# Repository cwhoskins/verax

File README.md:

# Verax

**Warning** This repo is under heavy design and should not be used under the belief that anything is stable or fully fleshed out.

Verax lets you describe a circuit, state what it must do, and check that by simulation. It is an embedded DSL in a Nim library: a design is a `.nim` file that declares nets, parts and subcircuits alongside the claims they must meet, and `verax check` proves or disproves each claim with graph walks, ngspice runs or a native signal-integrity engine.

The language is highly parameterizable and hierarchical in nature. Designs should be composed of subcircuits which have factory methods for design decisions and connected via standard interfaces and buses whenever possible.

## Example

```nim
import verax/contract/dsl
import verax/verify

let d = design("divider"):
  net gnd, kind = ntGround, name = "0"
  net vin, kind = ntPower:
    spec:
      voltage = 12.0.V
  net mid, kind = ntSignal

  component V1, kind = "voltage_source", value = "DC 12":
    pin "+", vin, kind = ptPower
    pin "-", gnd, kind = ptGround
  component R1, kind = "resistor", value = "30k":
    pin "1", vin, kind = ptPassive
    pin "2", mid, kind = ptPassive
  component R2, kind = "resistor", value = "10k":
    pin "1", mid, kind = ptPassive
    pin "2", gnd, kind = ptPassive

  role "power_rail", supply, rail = vin, voltage = 12.0.V, band = 5.pct
  require dc_voltage(mid) == 3.0.V, band = 1.pct, id = "REQ-DIV-TAP-001",
          because = "two 1% resistors give 1% worst case"

quit(verifyMain(d))
```

```
$ verax check templates/divider.nim
  spice.dc_voltage  [.op]  --  2 claim(s): 2 met
    [PASS]  REQ-DIV-TAP-001   dc_voltage(net 'mid')
             expect 3.00 V +-1.00% (2.97 V .. 3.03 V)   measured 3.00 V
    [PASS]  supply.voltage   dc_voltage(net 'vin')
             expect 12.0 V +-5.00% (11.4 V .. 12.6 V)   measured 12.0 V

checked 2 assertion(s): 2 passed, 0 failed, 0 not evaluated, 0 not evaluable
```

The full, commented version is `templates/divider.nim`.

## Features
- **Design contracts**: `role` bundles and `require` claims state what a circuit must do; each claim carries its tolerance band, an ID and a `because`. Static checks run without a simulator (`--offline`), and `--strict` fails on anything left unchecked
- Pin muxing built into parts and pin decisions automatically validated against the pin muxing table
- Standard interfaces automatically infer schematic analysis and auto-generated SPICE simulations
- **SPICE simulation** through ngspice (`.op`, `.dc`, `.ac`, `.tran`), with simulation-only device models and XSPICE code models (analog and digital) authored from Nim
- **Native signal-integrity engine** (no ngspice): IBIS drivers and receivers, packages, transmission lines and vias, crosstalk, differential pairs, PRBS/eye analysis and S-parameter channels
- IBIS sweeps pre-layout derive routing constraints, written out as KiCad `.kicad_dru` rules (`verax constraints`); `si_net` claims are then checked against the routed board (`--board=`)
- **Test reports**: `verax report` writes one self-contained HTML (or PDF) file with each test's circuit under test, setup, pass criteria, simulated circuit and bench, plots, verdicts and logs
- **Bill of materials**: `verax bom` resolves each part against catalogues and writes text, CSV or JSON; the JSON doubles as a lock file so part choices stay the same between builds
- **KiCad**: `verax layout` generates a starting `.kicad_pcb` with real footprints, and `.kicad_pcb` files round-trip byte-exact
- Parameterizable subcircuits with arbitrary factory methods so a part's recommended circuit can be implemented with desired settings
- Automatic topology view: a heuristic, deterministic schematic drawing (SVG/JSON) of each design — a readable picture, not a hand-laid-out sheet
- Ability for user to define roles, tests and analyses
- **Templates and discovery**: `verax new` writes a starter design; `verax roles`, `role <name>`, `quantities`, `annotations`, `interfaces` and `guide` list what a design can claim, straight from the live registries

## Requirements

- **Nim ≥ 2.2.10**. There are no dependencies beyond the Nim standard library.
- **Optional**, for the features that need them:
  - `ngspice` on `PATH`: SPICE simulation (without it, `--offline` checks still run)
  - `$NGSPICE_SRC` pointing at a configured ngspice source tree: building XSPICE code models
  - headless chromium, weasyprint or wkhtmltopdf on `PATH`: PDF reports (otherwise the HTML is kept)
  - KiCad footprint libraries (`$VERAX_FOOTPRINT_PATH`, or `/usr/share/kicad/footprints`): `verax layout`

`verax env` reports which of these it found.

## Install

```sh
git clone <this repo> verax && cd verax
nimble build          # builds ./bin/verax
```

## Quickstart

```sh
verax new rail foo.nim        # starter design (also: blank, i2c, divider, ...)
verax check foo.nim           # check every claim
verax check foo.nim --offline # graph walks only, no simulator
verax report foo.nim -o foo_report.html
verax guide                   # the authoring guide
```

## Where to look next

- `designs/` — example designs; `designs/datalogger/` is the largest, a full board split across sheets
- `templates/` — small commented starters, one idea each (what `verax new` writes)
- `docs/authoring.md` — writing a design
- `docs/architecture.md` — how the submodules relate
- `docs/findings.md` — what is open

## License

MIT — see `LICENSE`.

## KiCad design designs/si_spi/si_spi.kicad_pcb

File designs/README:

# Design files live here.
#
# Each is an ordinary Nim program that states what a circuit must do and
# ends with `quit(verifyMain(d))`. `nimble verify` checks every one.
#
# Start one with:  verax new rail designs/vdd.nim

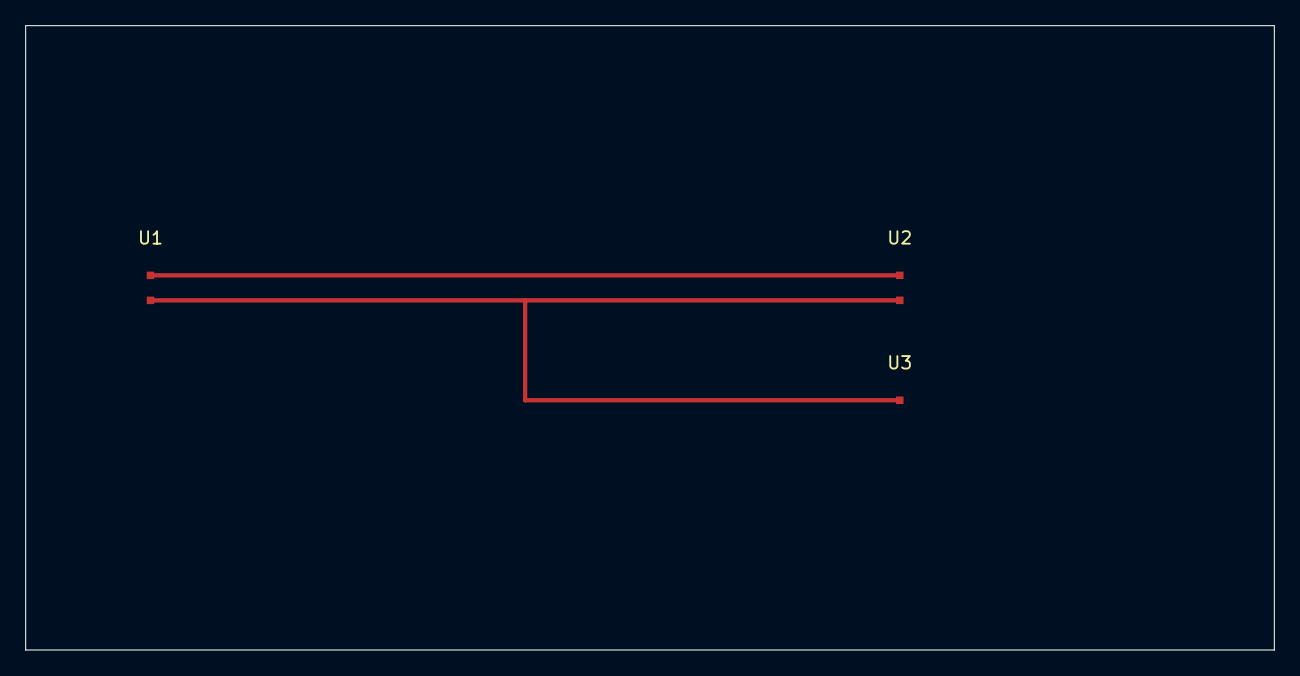
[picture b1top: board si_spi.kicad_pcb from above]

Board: 4 copper layers, 100.0 x 50.0 mm, 3 parts (0 on the bottom side), 2 nets.

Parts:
U1: U1; SOIC_STUB
U2: U2; SOIC_STUB
U3: U3; SOIC_STUB

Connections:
MOSI: U1.2, U2.2, U3.2
SCK: U1.1, U2.1
